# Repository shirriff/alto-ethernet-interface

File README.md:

# Alto Ethernet Interface

This project is an interface / gateway from the Xerox Alto's 3 Mb/s Ethernet
to the outside world.
The software runs on a [BeagleBone Black](http://beagleboard.org/bone) single-board Linux computer and uses a simple interface board (shield) to interface with the Alto's Ethernet.
This system makes use of the 
IFS file server software from [Living Computers Museum+Labs](http://livingcomputers.org).

## Background

Xerox PARC invented Ethernet in the 1970s, implementing 3 MB/s Ethernet on the Xerox Alto.
This was before TCP/IP and Xerox developed a network protocol called PUP (PARC Universal Packet) to run on Ethernet.
Xerox also built the IFS (Interim File Server), server software to support ftp, network boot, network disk copying, network services, gateways, and so forth.

The 3 MB/s Ethernet system consisted of several pieces.
A network interface board inside the Alto generated TTL signals.
The network itself consisted of a coaxial cable.
An external transceiver box translated between TTL signals and signals on the coaxial cable.
The TTL signals between the Alto and the transceiver consisted of the data from the Alto to the network, data to the Alto from the network, and a collision detection signal.

## Details of the interface

To hook the Alto up to a modern network, this project has several pieces:

 * A BeagleBone shield that interfaces to the Alto's Ethernet.
 * Gateway software on the BeagleBone to read/write packets.
 * The IFS file server running on the BeagleBone.
 
The BeagleBone processor includes two microcontrollers called PRUs.
This interface runs code on a PRU to send and receive the Ethernet data.
A C program communicates with the PRU and sends/receives the data locally
over UDP.
Finally, IFS also uses UDP to send/receive the packets, allowing the Alto to
communicate with IFS.

### The shield

The interface board plugs into the BeagleBone and simply translates signal
levels between the BeagleBone and the Alto.
A schematic and PCB design were created in KiCad, in the *board* directory.

### The Beaglebone software

 * The PRU code. This is written in C and is compiled using TI's Code Composer Studio.
 * The C gateway code.
 * The device tree overlay file, which sets the BeagleBone's pins correctly to communicate with the interface board.

The source code is in the *src* directory and pre-built binaries ready to install are in the *build* directory.

### IFS
 
The IFS software from [Living Computers Museum+Labs](http://livingcomputers.org).
This software is in C#. It can run on the BeagleBone using Mono.

The original IFS repository is [https://github.com/livingcomputermuseum/IFS](here://github.com/livingcomputermuseum/IFS).
My version of IFS with modified UDP support is [https://github.com/shirriff/IFS](https://github.com/shirriff/IFS).

## Installation

To configure a BeagleBone with this software, see [build/README.md](build/README.md).

## Use

Connect the Ethernet cable from the cape (i.e. the top board) to the Alto.
Boot the BeagleBone.
The 4 LEDs on the BeagleBone should flash randomly for about 35 seconds.
Then the LEDs should go out for a few seconds.
Then the first and last LEDs should blink briefly every second.

On the Alto, hold down backspace and apostrophe. Press the reset button on the back of the keyboard. Continue holding down backspace and apostrophe for a couple seconds until the cursor changes to a box of dots.
While this is happening, the first, second and fourth LED should be flashing a lot, indicating network traffic.
Hopefully the Alto will boot to the "Net Executive".
From here, type a question mark to list commands.
Type `astroroids` [sic] to boot the Asteroids game.
Type `ftp` for FTP. Note: it will hang with a two-box cursor if you don't have a disk running.
```
login test
open 1#
list *
```

You should be able to ssh into the BeagleBone as 192.168.4.5 if necessary.

## Notes

LEDS:
* 0 (Left): sending packet to Alto
* 1: received packet from Alto
* 2: timeout (5 seconds with no activity)
* 3: select loop (gateway alive)

(To create IFS.tgz: tar -czvf IFS.tgz IFS)
To check systemd: `systemctl status alto-gateway.service` (or alto-ifs.service)
Also look in /var/log/syslog for errors

For background on the BeagleBone, see my articles on the [BeagleBone PRU](http://www.righto.com/2016/08/pru-tips-understanding-beaglebones.html) and [PRU C compiler](http://www.righto.com/2016/09/how-to-run-c-programs-on-beaglebones.html).

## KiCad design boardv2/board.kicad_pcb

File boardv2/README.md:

# Instructions for building the board (obsolete)

Note: this version of the board has been replaced by boardv3.

The board was designed with KiCad. This directory contains the KiCad files.
The board can be ordered from OshPark [here](https://oshpark.com/shared_projects/5WJDIPzl).

## Materials

* 7438 open-collector NAND gate.
* 2 x [2x23 Male Headers](https://www.adafruit.com/product/2076)
* 2 x [0.1uF ceramic capacitor](https://www.adafruit.com/product/753)
* R1: 120 ohm resistor
* R2: 330 ohm resistor
* Ethernet connector: through-hole, PCB mount RJ45
* DB25 male to RJ45 female modular adapter kit ([ADM-25M8-BK](http://www.frys.com/product/1544923))
* Ethernet cable
* BeagleBone Black + power supply + network connection (e.g. Apple Thunderbolt to Ethernet)

## DB25 connector wiring
 * 3 Blue
 * 16 Orange

 * 8 Red
 * 20 Green

 * 12 Yellow
 * 24 Black

 * 13 White
 * 25 Brown

Insert pins from back. Pin 1 is left on the wider side. Push pins in until they click.
You can twist the pairs of wires together if you want.

<pre>
W Y . . . R . . . . L . .
 N K . . . G . . . O . .
</pre>
(L = blue, N = brown, K = black)

## Testing

Output signal to Alto can be measured across pins 1 and 3 of the IC (pin 1 = ground). When connected to Alto, signal should be idle low (0.5V), pulsing to 4.5V. Can be a bit of overshoot, but shouldn't be ringing.
When disconnected from Alto, signal should go between 0V and 5V.

Input signal from Alto can be measured across the right hand side of a resistor. Signal should be idle high (2.2V) pulsing to 0V.

## LEDS

0 = top, 3 = closest to Ethernet port.
0 and 3 should flash every 2 seconds for Breath-of-life packet.
Others should flash during network boot or other network traffic.
If LED 0 is stuck on, reboot the BeagleBone. (There's something wrong with the gateway.)

At the end of a disk boot, LED 1 should flash a couple times (as the Alto does a couple network requests).

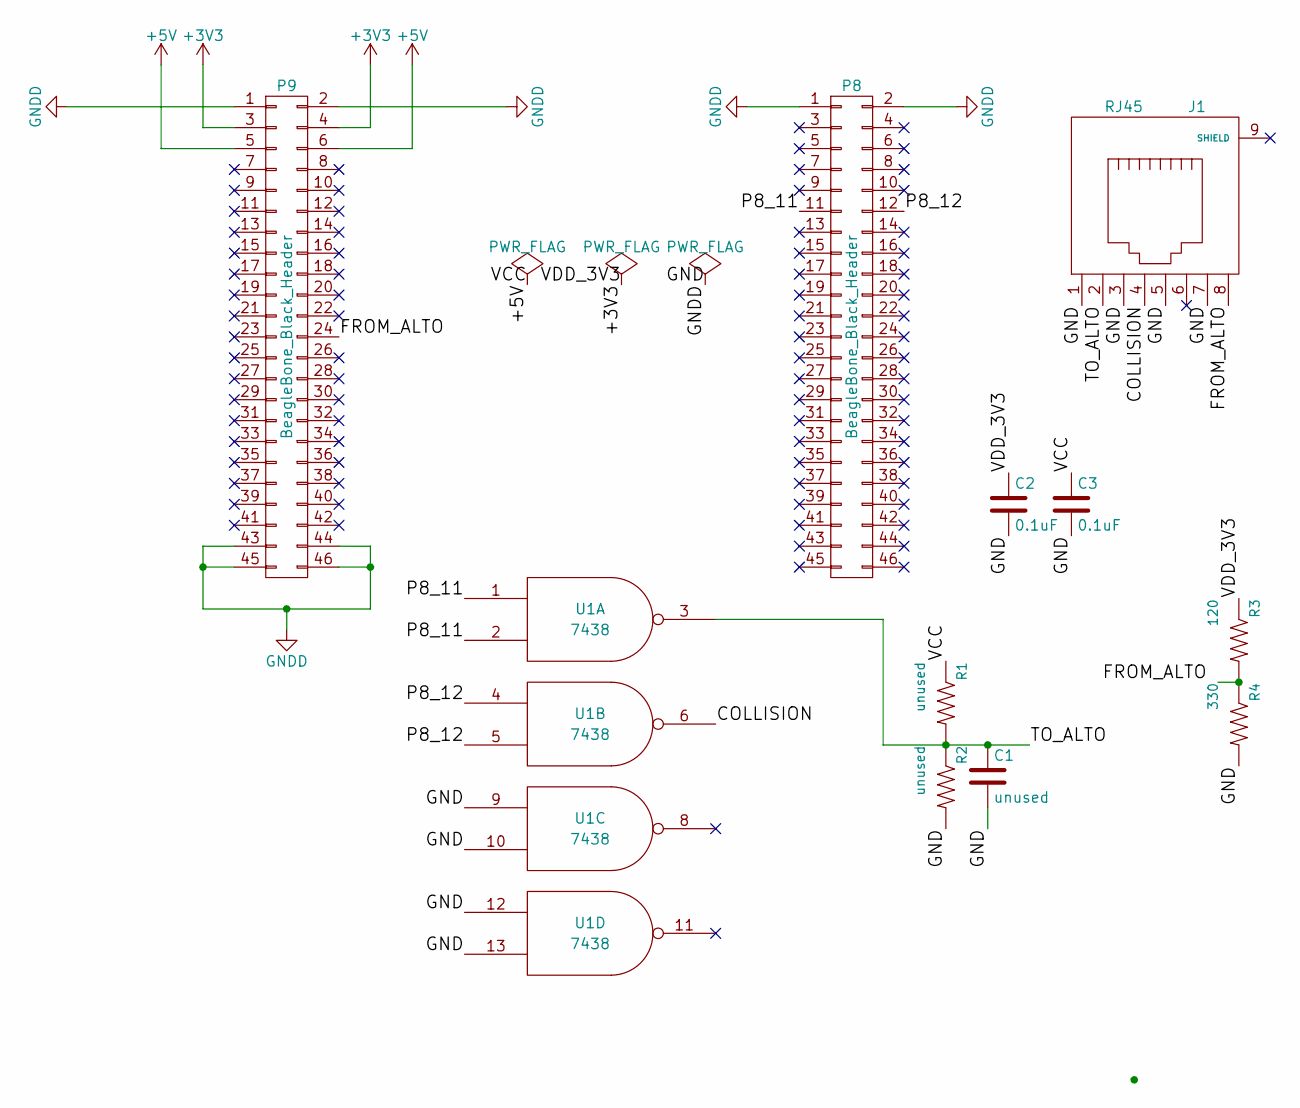
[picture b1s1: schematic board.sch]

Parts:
C1: unused; C_Disc_D3.0mm_W1.6mm_P2.50mm
C2, C3: 0.1uF; C_Disc_D3.0mm_W1.6mm_P2.50mm
J1: RJ45; RJ45_8
P8, P9: BeagleBone_Black_Header; Socket_BeagleBone_Black
R1, R2: unused; AXIAL-0.3
R3: 120; AXIAL-0.3
R4: 330; AXIAL-0.3
U1: 7438; DIP-14_W7.62mm

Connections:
+3V3: C2.1, P9.3, P9.4, R3.P$1 (1)
+5V: C3.1, P9.5, P9.6, R1.P$1 (1), U1.14 (VCC)
/COLLISION: J1.4, U1.6
/FROM_ALTO: J1.8, P9.24
/P8_11: P8.11, U1.1, U1.2
/P8_12: P8.12, U1.4, U1.5
/TO_ALTO: C1.1, J1.2, R1.P$2 (2), R2.P$1 (1), U1.3
GND: C1.2, C2.2, C3.2, J1.1, J1.3, J1.5, J1.7, P8.1, P8.2, P9.1, P9.2, P9.43, P9.44, P9.45, P9.46, R2.P$2 (2), R4.P$2 (2), U1.7 (GND), U1.9, U1.10, U1.12, U1.13
unnamed: R3.P$2 (2), R4.P$1 (1)

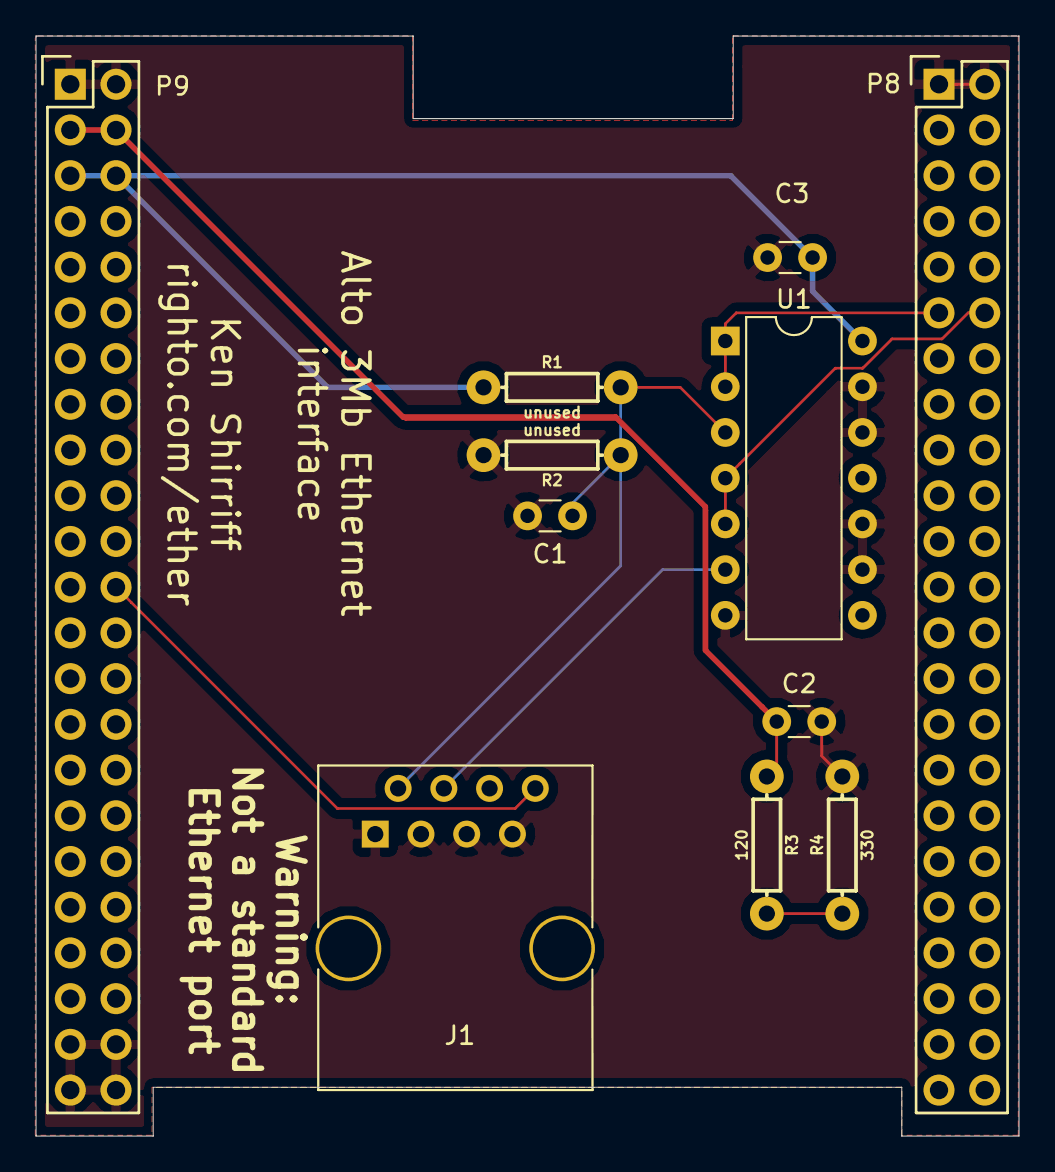
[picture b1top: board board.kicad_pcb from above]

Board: 2 copper layers, 54.6 x 61.1 mm, 11 parts (0 on the bottom side), 9 nets.

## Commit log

2017-10-12 Initial commit.
2017-10-13 Interface board design.
2017-10-13 Add built files
2017-10-13 Replace ethertext.bin with working version.
2017-10-18 Fix race condition
2017-10-24 Updated binary files
2017-10-27 Fix PUP checksum bug (drop Ether CRC from received packet). Clean up code.
2017-10-27 etherNet: add logging, verbose options. Clean up code.
2017-10-27 Rename etherNet.c to gateway.c
2017-11-08 Change synchronization model: read and write buffers owned by PRU or ARM Also remove delay in starting read; was dropping packets received just after write.
2017-11-09 Fix bug with double-clearing events.
2017-12-05 Working version.
2017-12-13 Schematic of board.
2017-12-20 Add version 2 of the board.
2018-01-08 Update README, indicating boardv2 is obsolete
2018-01-08 Add v3 of board design.
2018-01-08 Rename boardv2 to board. Replace the Eagle version with the KiCad version
2018-01-08 Rename directories
2018-01-26 Changes to support v2/v3 board.
    The driver chip in the v2/v3 board inverts polarity, so the gateway code
    needs to flip polarity of the outgoing data and collision signal.
    ethertext.bin is updated with the new code.
    Note: to use the v1 board, you need to use ethertext.bin.v1.
2018-01-26 Update README with v3 info.
2018-02-05 Add instructions for using disk image.
2018-02-05 Add note on SD installation.
2020-05-28 Fix pin number typo.
2020-05-28 Fix pin typo
